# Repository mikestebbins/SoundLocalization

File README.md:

SoundLocalization
=================

A few projects for doing sound localization using multiple mics on a teensy 3.1

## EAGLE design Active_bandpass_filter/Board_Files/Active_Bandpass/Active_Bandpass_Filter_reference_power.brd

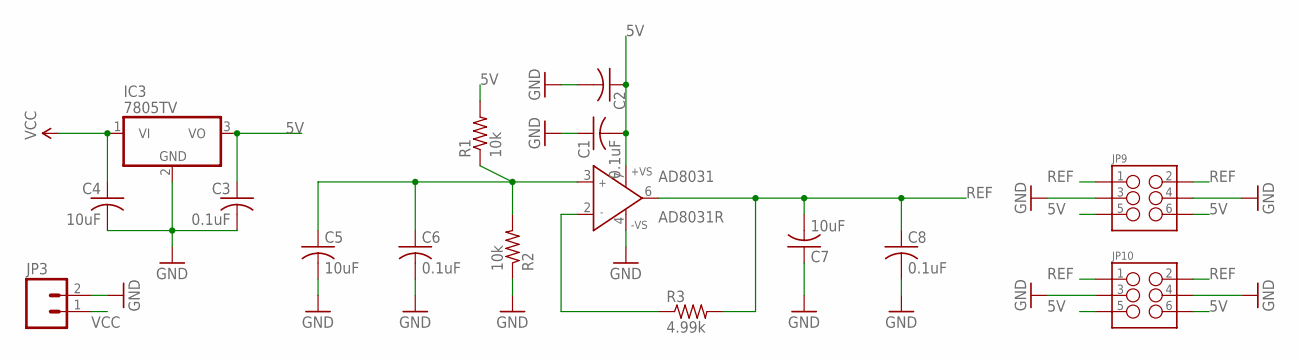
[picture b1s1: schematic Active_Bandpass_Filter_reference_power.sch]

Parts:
AD8031: AD8031R; SO8
C1, C3, C6, C8: 0.1uF; C1206
C2: C-USC1206; C1206
C4, C5, C7: 10uF; C1206
IC3: 7805TV; TO220V
JP3: M02LOCK_LONGPADS; 1X02_LOCK_LONGPADS
JP9, JP10: M03X22X3_SILK_MALE_PTH; 2X3
R1, R2: 10k; R1206
R3: 4.99k; R1206

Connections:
5V: AD8031.7 (+VS), C1.2, C2.1, C3.1, IC3.3 (VO), JP9.5, JP9.6, JP10.5, JP10.6, R1.2
C5: AD8031.3 (IN+), C5.1, C6.1, R1.1, R2.2
GND: AD8031.4 (-VS), C1.1, C2.2, C3.2, C4.2, C5.2, C6.2, C7.1, C8.2, IC3.2 (GND), JP3.2, JP9.3, JP9.4, JP10.3, JP10.4, R2.1
unnamed: AD8031.2 (IN-), R3.1
REF: AD8031.6 (OUT), C7.2, C8.1, JP9.1, JP9.2, JP10.1, JP10.2, R3.2
VCC: C4.1, IC3.1 (VI), JP3.1

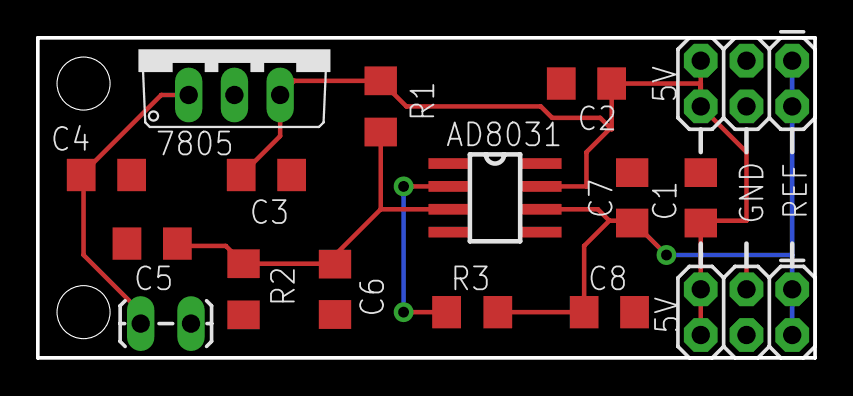
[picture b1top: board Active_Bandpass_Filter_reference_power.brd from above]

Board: 2 copper layers, 43.2 x 17.8 mm, 16 parts (0 on the bottom side), 6 nets.

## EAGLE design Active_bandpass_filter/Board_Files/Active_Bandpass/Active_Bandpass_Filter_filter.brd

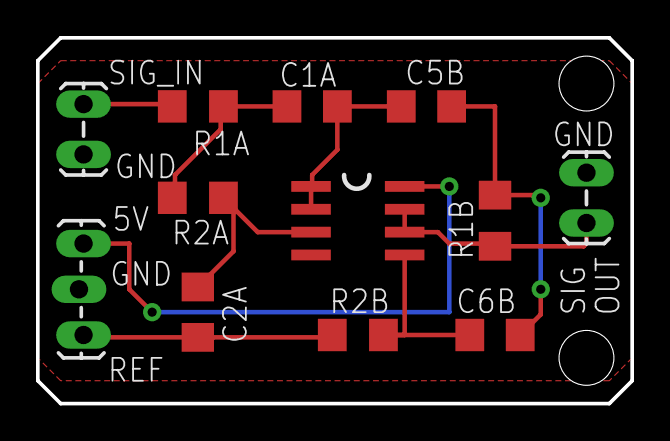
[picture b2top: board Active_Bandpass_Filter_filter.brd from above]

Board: 2 copper layers, 33.0 x 20.3 mm, 12 parts (0 on the bottom side), 10 nets.

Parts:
C1A: 3.9nF; C1206
C2A: 390pF; C1206
C5B, C6B: 68nF; C1206
IC5: AD8542R; SO8
JP1, JP2: 1X02_LOCK_LONGPADS
JP4: 1X03_LOCK_LONGPADS
R1A: 8.45k; R1206
R1B: 6.34k; R1206
R2A: 118k; R1206
R2B: 15.8k; R1206

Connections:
5V: IC5.8, JP4.1
GND: IC5.4, JP1.1, JP2.1, JP4.2
unnamed: C1A.1, R1A.2, R2A.1
unnamed: C2A.1, IC5.3, R2A.2
unnamed: C1A.2, C5B.1, IC5.1, IC5.2
unnamed: C5B.2, C6B.1, R1B.1
unnamed: C6B.2, IC5.5, R2B.2
REF: C2A.2, JP4.3, R2B.1
SIG_IN: JP1.2, R1A.1
SIG_OUT: IC5.6, IC5.7, JP2.2, R1B.2

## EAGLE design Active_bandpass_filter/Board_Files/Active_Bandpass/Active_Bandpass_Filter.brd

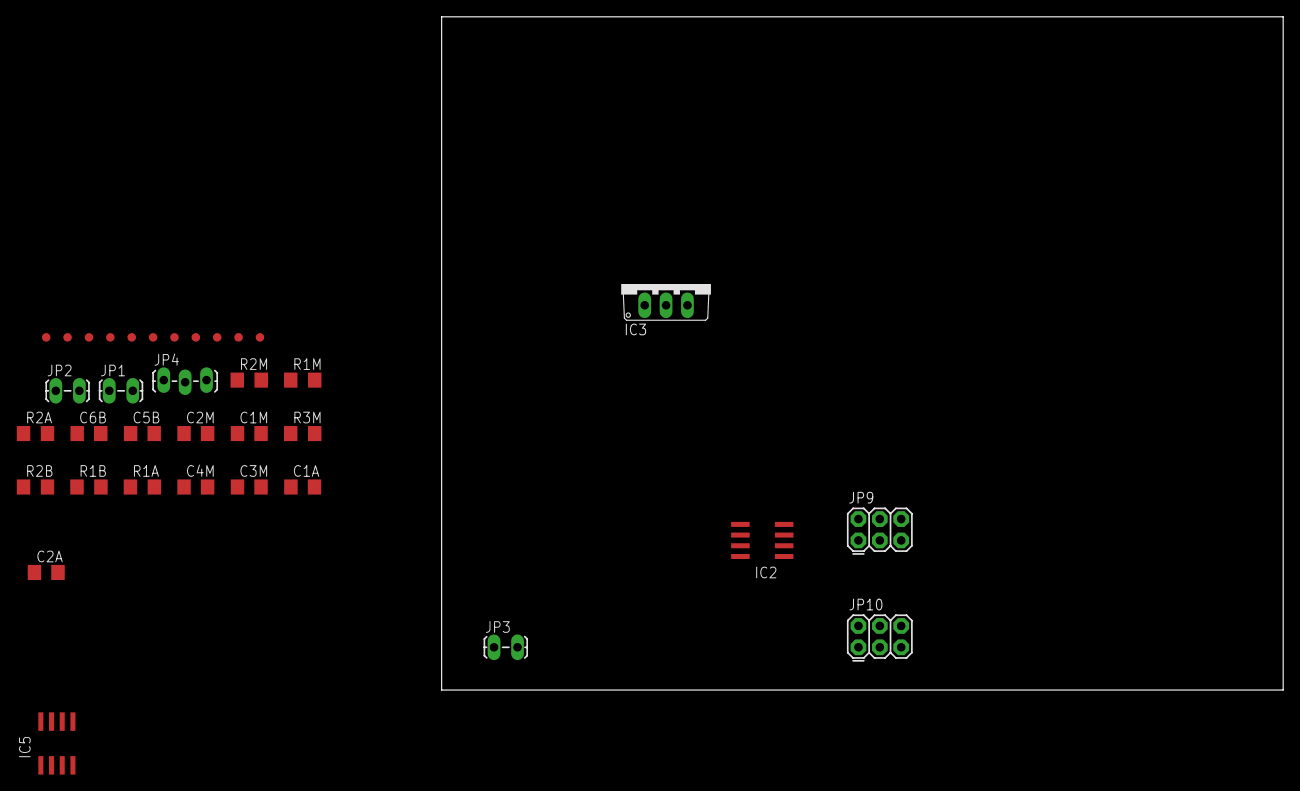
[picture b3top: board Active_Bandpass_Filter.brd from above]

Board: 2 copper layers, 100.0 x 80.0 mm, 35 parts (0 on the bottom side), 13 nets, no tracks yet.

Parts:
C1A: 3.9nF; C1206
C1M, C2M: 10uF; C1206
C2A: 390pF; C1206
C3M, C4M: 0.1uF; C1206
C5B, C6B: 68nF; C1206
IC2: AD8031R; SO8
IC3: 7805TV; TO220V
IC5: AD8542R; SO8
JP1, JP2, JP3: 1X02_LOCK_LONGPADS
JP4: 1X03_LOCK_LONGPADS
JP9, JP10: 2X3
R1A: 8.45k; R1206
R1B: 6.34k; R1206
R1M, R2M: 10k; R1206
R2A: 118k; R1206
R2B: 15.8k; R1206
R3M: 4.99k; R1206
TP1, TP2, TP3, TP4, TP5, TP6, TP7, TP8, TP9, TP10, TP11: TEST-POINT3X4; PAD.03X.04

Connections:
5V: IC2.7, IC3.3, IC5.8, JP4.1, JP9.5, JP9.6, JP10.5, JP10.6, R1M.2, TP6.P$1, TP9.P$1, TP10.P$1
GND: C1M.2, C2M.2, C3M.2, C4M.2, IC2.4, IC3.2, IC5.4, JP1.1, JP2.1, JP3.2, JP4.2, JP9.3, JP9.4, JP10.3, JP10.4, R2M.1, TP7.P$1, TP8.P$1, TP11.P$1
unnamed: C1A.1, R1A.2, R2A.1
unnamed: C2A.1, IC5.3, R2A.2
unnamed: C1A.2, C5B.1, IC5.1, IC5.2, TP1.P$1
unnamed: C5B.2, C6B.1, R1B.1
unnamed: C6B.2, IC5.5, R2B.2
unnamed: C1M.1, C4M.1, IC2.3, R1M.1, R2M.2
unnamed: IC2.2, R3M.1
REF: C2A.2, C2M.1, C3M.1, IC2.6, JP4.3, JP9.1, JP9.2, JP10.1, JP10.2, R2B.1, R3M.2, TP2.P$1, TP4.P$1
SIG_IN: R1A.1, TP3.P$1
SIG_OUT: IC5.6, IC5.7, JP2.2, R1B.2, TP5.P$1
VCC: IC3.1, JP3.1

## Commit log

2015-12-15 Initialize
2015-12-15 split into 2 boards
2015-12-16 add Analog Devices design files for the eval boards I used during summer
2015-12-17 first real attempt at routing power board
2015-12-17 invoice for Mouser order
2015-12-20 reference power board routed completely
2015-12-20 routing, DRC, Ratsnest all okay
2015-12-21 finalized silk screen, submit to OSH Park
2015-12-21 fix a few duplicated silkscreens found in OSH park upload
2015-12-21 more silkscreen fixes
2015-12-21 Initial board buildup for individual filter board

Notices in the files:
parts and their libraries:
SparkFun-Connectors: Licensing: Creative Commons ShareAlike 4.0 International - https://creativecommons.org/licenses/by-sa/4.0
